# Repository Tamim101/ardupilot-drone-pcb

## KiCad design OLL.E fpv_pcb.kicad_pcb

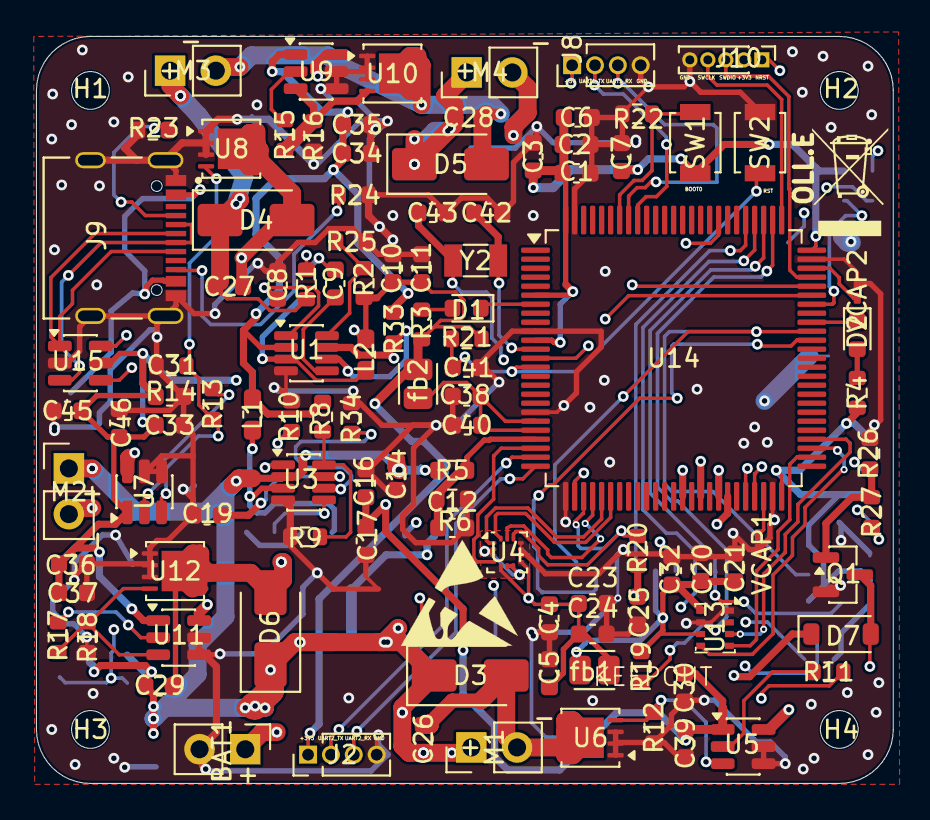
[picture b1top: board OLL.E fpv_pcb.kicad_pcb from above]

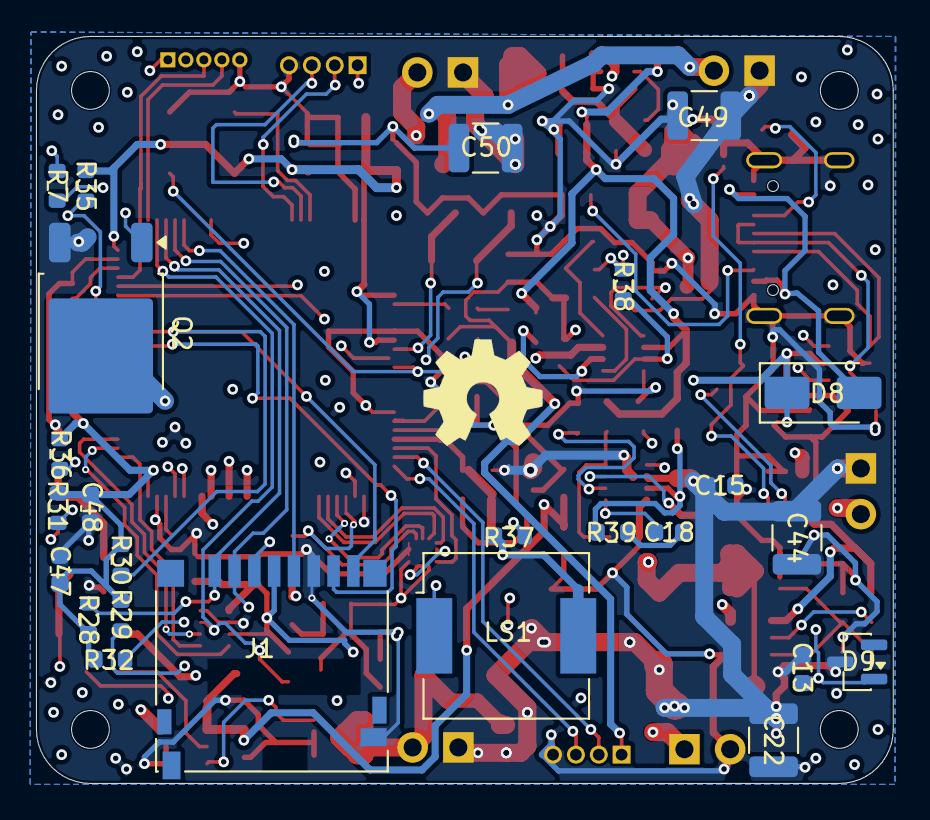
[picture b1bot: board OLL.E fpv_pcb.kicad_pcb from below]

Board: 6 copper layers, 47.6 x 41.5 mm, 138 parts (25 on the bottom side), 82 nets.

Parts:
BAT1: Conn_01x02_Pin; PinHeader_1x02_P2.54mm_Vertical
C1, C2, C3, C6, C8, C9, C12, C13, C14, C18, C19, C20, C32, C38, C41, C46, C47: 100nF; C_0603_1608Metric
C4, C33, C35, C37, C39, C40: 1uF; C_0603_1608Metric
C5, C15, C21, C48: 10uF; C_0603_1608Metric
C7, C11, C45: 4.7uF; C_0603_1608Metric
C10, C16: 22uF; C_0603_1608Metric
C17: 22uF/16v; C_0603_1608Metric
C22, C44, C49, C50: 22uF; C_1210_3225Metric
C23: 10nF; C_0603_1608Metric
C24: 0.1uF; C_0603_1608Metric
C25: 2.2uF; C_0603_1608Metric
C26, C27, C28, C29: 100nf; C_0603_1608Metric
C30, C31, C34, C36: 100nF/50v; C_0603_1608Metric
C42, C43: 15pF; C_0603_1608Metric
D1, D2: led; LED_0603_1608Metric
D3, D4, D5, D6: SS54FSH; D_SMA
D7: 1N4148W; D_SOD-123
D8: SS14; D_SMA
D9: BZX84C10; SOT-23
H1, H2, H3, H4: MountingHole; MountingHole_2.1mm
J1: Micro_SD_Card; microSD_HC_Hirose_DM3D-SF
J2: RC; PinHeader_1x04_P1.27mm_Vertical
J8: reciver; PinHeader_1x04_P1.27mm_Vertical
J9: TYPE-C-31-M-12; HRO_TYPE-C-31-M-12
J10: Conn_01x05_Pin; PinHeader_1x05_P1.00mm_Vertical
L1, L2: 4.7uH; L_0603_1608Metric_Pad1.05x0.95mm_HandSolder
LS1: CMT-7525-80-SMT-TR; Buzzer_CUI_CPT-9019S-SMT
M1: M1 front left; PinHeader_1x02_P2.54mm_Vertical
M2: M2 front right; PinHeader_1x02_P2.54mm_Vertical
M3: M3 rear right; PinHeader_1x02_P2.54mm_Vertical
M4: m4 rear left; PinHeader_1x02_P2.54mm_Vertical
Q1: 2N7002; SOT-23
Q2: SUD45P03-09; TO-252-2
R1, R10, R33: 100k; R_0603_1608Metric
R2: 31.6k; R_0603_1608Metric
R3, R4: 1k; R_0603_1608Metric
R5: 22k; R_0603_1608Metric
R6, R9, R12, R14, R16, R18, R20, R21, R22, R25, R26, R35, R36: 10k; R_0603_1608Metric
R7: 0 ohm; R_0603_1608Metric
R8: 52.3k; R_0603_1608Metric
R11, R13, R15, R17: 33; R_0603_1608Metric
R19: 10K; R_0603_1608Metric
R23, R24: 5.1k; R_0603_1608Metric
R27: 100; R_0603_1608Metric
R28, R29, R30, R31, R32: 47k; R_0603_1608Metric
R34: 33k; R_0603_1608Metric
R37: 18 ohm; R_0603_1608Metric
R38, R39: 20 ohm; R_0603_1608Metric
SW1, SW2: SW_SPST; SW_SPST_B3U-1000P
U1, U3: MP2315GJ; SOT-23-8
U4: ICM-42688-P; LGA-14_2x2mm_P0.35mm_LayoutBorder3x4y
U5, U7, U9, U11: UCC27511ADBV; SOT-23-6
U6: ul_AON7410; DFN-8-1EP_3x3mm_P0.65mm_EP1.5x2.25mm
U8, U10, U12: AON7410; DFN-8-1EP_3x3mm_P0.65mm_EP1.5x2.25mm
U13: BMP280; Bosch_LGA-8_2x2.5mm_P0.65mm_ClockwisePinNumbering
U14: STM32H753VITx; LQFP-100_14x14mm_P0.5mm
U15: USBLC6-2SC6; SOT-23-6
VCAP1, VCAP2: 2.2uF; C_0201_0603Metric_Pad0.64x0.40mm_HandSolder
Y2: 8HMz; Crystal_SMD_3215-2Pin_3.2x1.5mm
fb1, fb2: 600 ohm 100mHZ; L_Eaton_MCL2012V1

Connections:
+3V3_FC: C1.1 (+), C2.1 (+), C3.1 (+), C6.1 (+), C7.1 (+), C10.1 (+), C11.1 (+), C20.2 (-), C21.1 (+), C32.1 (+), C47.1 (+), C48.1 (+), J1.4 (VDD), J2.1, J10.2, L2.2 (-), R2.2 (-), R3.1 (+), R4.1 (+), R19.2 (-), R21.2 (-), R28.1 (+), R29.1 (+), R30.1 (+), R31.2 (-), R32.1 (+), R35.2 (-), R36.2 (-), SW1.1 (A), U13.6 (VDDIO), U13.8 (VDD), U14.6 (VBAT), U14.11 (VDD), U14.27 (VDD), U14.50 (VDD), U14.75 (VDD), U14.100 (VDD), fb1.2, fb2.1
+3V3_IMU: C4.1 (+), C5.1 (+), C23.1 (+), C24.1 (+), C25.2 (-), R20.1 (+), U4.5 (VDDIO), U4.8 (VDD), fb1.1
+5V_FC: C16.1 (+), C17.1 (+), C30.1 (+), C31.1 (+), C33.1 (+), C34.1 (+), C35.1 (+), C36.1 (+), C37.1 (+), C39.1 (+), C45.1 (+), C46.1 (+), D8.1 (K), J8.1, L1.2 (-), R8.2 (-), R33.2 (-), R37.1 (+), U1.2 (IN), U5.1 (V_{DD}), U7.1 (V_{DD}), U9.1 (V_{DD}), U11.1 (V_{DD}), U15.5 (VBUS)
+VBAT: C13.2 (-), C14.2 (-), C15.1 (+), C22.2 (-), C26.1 (+), C27.1 (+), C28.1 (+), C29.1 (+), C44.2 (-), C49.2 (-), C50.2 (-), D3.1, D4.1, D5.1, D6.1, D9.3 (K), M1.1, M2.1, M3.1, M4.1, Q2.3 (S), R1.1 (+), R5.2 (-), U3.2 (IN)
/VBAT_RAW: BAT1.1, Q2.2 (D)
ADC_VBAT: C12.1 (+), R5.1 (+), R6.2 (-), U14.22 (PA0)
BARO_CS: R19.1 (+), U13.2 (CSB), U14.77 (PA15)
BEEPER: R27.1 (+), U14.46 (PB10)
BOOT0: R22.2 (-), SW1.2 (B), U14.94 (BOOT0)
C1_D0: J1.7 (DAT0), R29.2 (-), U14.65 (PC8)
C1_D1: J1.8 (DAT1), R30.2 (-), U14.66 (PC9)
C1_D2: J1.1 (DAT2), R28.2 (-), U14.78 (PC10)
C1_D3: J1.2 (DAT3/CD), R32.2 (-), U14.79 (PC11)
CLK: J1.5 (CLK), U14.80 (PC12)
CMD: J1.3 (CMD), R31.1 (+), U14.83 (PD2)
GND: BAT1.2, C1.2 (-), C2.2 (-), C3.2 (-), C4.2 (-), C5.2 (-), C6.2 (-), C7.2 (-), C8.2 (-), C10.2 (-), C11.2 (-), C12.2 (-), C14.1 (+), C15.2 (-), C16.2 (-), C17.2 (-), C19.2 (-), C20.1 (+), C21.2 (-), C22.1 (+), C23.2 (-), C24.2 (-), C25.1 (+), C30.2 (-), C31.2 (-), C32.2 (-), C33.2 (-), C34.2 (-), C35.2 (-), C36.2 (-), C37.2 (-), C38.2 (-), C39.2 (-), C40.2 (-), C41.2 (-), C42.2 (-), C43.2 (-), C44.1 (+), C45.2 (-), C46.2 (-), C47.2 (-), C48.2 (-), C49.1 (+), C50.1 (+), J1.6 (VSS), J1.9 (SHIELD), J2.4, J8.4, J9.A1_B12 (GND), J9.B1_A12 (GND), J9.S1 (SHIELD), J9.S2 (SHIELD), J9.S3 (SHIELD), J9.S4 (SHIELD), J10.5, Q1.2 (S), R6.1 (+), R9.1 (+), R10.2 (-), R12.2 (-), R14.2 (-), R16.2 (-), R18.2 (-), R22.1 (+), R23.1 (+), R24.1 (+), R25.1 (+), R26.2 (-), R34.2 (-), SW2.2 (B), U1.4 (GND), U3.4 (GND), U4.2 (RESV_2), U4.3 (RESV_3), U4.6 (GND), U4.7 (RESV_7), U4.9 (INT2/FSYNC/CLKIN), U4.10 (RESV_10), U4.11 (RESV_11), U5.4 (GND), U5.5 (IN-), U6.1 (S), U6.2 (S), U6.3 (S), U7.4 (GND), U7.5 (IN-), U8.1 (S), U8.2 (S), U8.3 (S), U9.4 (GND), U9.5 (IN-), U10.1 (S), U10.2 (S), U10.3 (S), U11.4 (GND), U11.5 (IN-), U12.1 (S), U12.2 (S), U12.3 (S), U13.1 (GND), U13.7 (GND), U14.10 (VSS), U14.19 (VSSA), U14.26 (VSS), U14.49 (VSS), U14.74 (VSS), U14.99 (VSS), U15.2 (GND), VCAP1.1 (+), VCAP2.1 (+)
GYRO_CS: R20.2 (-), U4.12 (AP_CS), U14.28 (PA4)
GYRO_INT: U4.4 (INT1/INT), U14.23 (PA1)
LED0: D1.1, U14.7 (PC13)
LED1_ARM: D2.1, U14.67 (PA8)
MOTOR1: U5.6 (IN+), U14.39 (PE9)
MOTOR2: U7.6 (IN+), U14.41 (PE11)
MOTOR3: U9.6 (IN+), U14.43 (PE13)
MOTOR4: U11.6 (IN+), U14.44 (PE14)
NRST: C41.1 (+), J10.1, R21.1 (+), SW2.1 (A), U14.14 (NRST)
unnamed: C8.1 (+), U1.1 (AAM), U1.7 (VCC)
unnamed: C9.1 (+), U1.5 (BST)
unnamed: C9.2 (-), R38.1 (+)
unnamed: C13.1 (+), D9.1 (A), Q2.1 (G), R10.1 (+)
unnamed: C18.1 (+), U3.5 (BST)
unnamed: C18.2 (-), R39.1 (+)
unnamed: C19.1 (+), U3.1 (AAM), U3.7 (VCC)
unnamed: C26.2 (-), D3.2, M1.2, U6.5 (D), U6.6 (D), U6.7 (D), U6.8 (D), U6.9 (EPAD)
unnamed: C27.2 (-), D4.2, M2.2, U8.5 (D), U8.6 (D), U8.7 (D), U8.8 (D), U8.9 (EPAD)
unnamed: C28.2 (-), D5.2, M3.2, U10.5 (D), U10.6 (D), U10.7 (D), U10.8 (D), U10.9 (EPAD)
unnamed: C29.2 (-), D6.2, M4.2, U12.5 (D), U12.6 (D), U12.7 (D), U12.8 (D), U12.9 (EPAD)
unnamed: C42.1 (+), U14.12 (PH0), Y2.1
unnamed: C43.1 (+), R7.1 (+), Y2.2
unnamed: D7.2 (A), LS1.1, Q1.3 (D)
unnamed: D7.1 (K), LS1.2, R37.2 (-)
unnamed: J9.A5 (CC1), R23.2 (-)
unnamed: J9.B5 (CC2), R24.2 (-)
unnamed: J9.A7 (DN1), J9.B7 (DN2), U15.3 (I/O2)
unnamed: J9.A6 (DP1), J9.B6 (DP2), U15.1 (I/O1)
unnamed: L1.1 (+), R39.2 (-), U3.3 (SW)
unnamed: L2.1 (+), R38.2 (-), U1.3 (SW)
unnamed: Q1.1 (G), R26.1 (+), R27.2 (-)
unnamed: R1.2 (-), R34.1 (+), U3.6 (EN/SYNC)
unnamed: R2.1 (+), R25.2 (-), U1.8 (FB)
unnamed: D1.2, R3.2 (-)
unnamed: D2.2, R4.2 (-)
unnamed: R7.2 (-), U14.13 (PH1)
unnamed: R8.1 (+), R9.2 (-), U3.8 (FB)
unnamed: R11.1 (+), R12.1 (+), U5.3 (OUTL), U6.4 (G)
unnamed: R11.2 (-), U5.2 (OUTH)
unnamed: R13.1 (+), R14.1 (+), U7.3 (OUTL), U8.4 (G)
unnamed: R13.2 (-), U7.2 (OUTH)
unnamed: R15.1 (+), R16.1 (+), U9.3 (OUTL), U10.4 (G)
unnamed: R15.2 (-), U9.2 (OUTH)
unnamed: R17.1 (+), R18.1 (+), U11.3 (OUTL), U12.4 (G)
unnamed: R17.2 (-), U11.2 (OUTH)
unnamed: R33.1 (+), U1.6 (EN/SYNC)
unnamed: R35.1 (+), U14.69 (PA10)
unnamed: R36.1 (+), U14.47 (PB11)
unnamed: U14.48 (VCAP), VCAP1.2 (-)
unnamed: U14.73 (VCAP), VCAP2.2 (-)
SPI1_SCK: U4.13 (AP_SCL/AP_SCLK), U14.29 (PA5)
SPI1_SDI: U4.14 (AP_SDA/AP_SDIO/AP_SDI), U14.31 (PA7)
SPI1_SDO: U4.1 (AP_SDO/AP_AD0), U14.30 (PA6)
SPI2_SCK: U13.4 (SCK), U14.52 (PB13)
SPI2_SDI: U13.3 (SDI), U14.54 (PB15)
SPI2_SDO: U13.5 (SDO), U14.53 (PB14)
SWCLK: J10.4, U14.76 (PA14)
SWDIO: J10.3, U14.72 (PA13)
UART1_RX: J8.3, U14.93 (PB7)
UART1_TX: J8.2, U14.92 (PB6)
UART2_RX: J2.3, U14.25 (PA3)
UART2_TX: J2.2, U14.24 (PA2)
USB D+: U14.71 (PA12), U15.6 (I/O1)
USB D−: U14.70 (PA11), U15.4 (I/O2)
VBUS: D8.2 (A), J9.A4_B9 (VBUS), J9.B4_A9 (VBUS)
VDDA_FILT: C38.1 (+), C40.1 (+), U14.20 (VREF+), U14.21 (VDDA), fb2.2

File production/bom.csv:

Designator,Footprint,Quantity,Value,LCSC Part #
BAT1,PinHeader_1x02_P2.54mm_Vertical,1,Conn_01x02_Pin,
"C1, C12, C13, C14, C18, C19, C2, C20, C26, C27, C28, C29, C3, C32, C38, C41, C46, C47, C6, C8, C9",0603,21,100nF,
"C10, C16",0603,2,22uF,
"C11, C45, C7",0603,3,4.7uF,
"C15, C21, C48, C5",0603,4,10uF,
C17,0603,1,22uF/16v,
"C22, C44, C49, C50",1210,4,22uF,
C23,0603,1,10nF,
C24,0603,1,0.1uF,
C25,0603,1,2.2uF,
"C30, C31, C34, C36",0603,4,100nF/50v,
"C33, C35, C37, C39, C4, C40",0603,6,1uF,
"C42, C43",0603,2,15pF,
"D1, D2",0603,2,led,
"D3, D4, D5, D6",D_SMA,4,SS54FSH,
D7,D_SOD-123,1,1N4148W,
D8,D_SMA,1,SS14,
D9,SOT-23,1,BZX84C10,
"FB1, FB2",L_Eaton_MCL2012V1,2,600 ohm 100mHZ,
J1,microSD_HC_Hirose_DM3D-SF,1,Micro_SD_Card,
J10,PinHeader_1x05_P1.00mm_Vertical,1,Conn_01x05_Pin,
J2,PinHeader_1x04_P1.27mm_Vertical,1,RC,
J8,PinHeader_1x04_P1.27mm_Vertical,1,reciver,
J9,HRO_TYPE-C-31-M-12,1,TYPE-C-31-M-12,
"L1, L2",0603,2,4.7uH,
LS1,Buzzer_CUI_CPT-9019S-SMT,1,CMT-7525-80-SMT-TR,
M1,PinHeader_1x02_P2.54mm_Vertical,1,M1 front left,
M2,PinHeader_1x02_P2.54mm_Vertical,1,M2 front right,
M3,PinHeader_1x02_P2.54mm_Vertical,1,M3 rear right,
M4,PinHeader_1x02_P2.54mm_Vertical,1,m4 rear left,
Q1,SOT-23,1,2N7002,
Q2,TO-252-2,1,SUD45P03-09,
"R1, R10, R33",0603,3,100k,
"R11, R13, R15, R17",0603,4,33,
"R12, R14, R16, R18, R19, R20, R21, R22, R25, R26, R35, R36, R6, R9",0603,14,10k,
R2,0603,1,31.6k,
"R23, R24",0603,2,5.1k,
R27,0603,1,100,
"R28, R29, R30, R31, R32",0603,5,47k,
"R3, R4",0603,2,1k,
R34,0603,1,33k,
R37,0603,1,18 ohm,
"R38, R39",0603,2,20 ohm,
R5,0603,1,22k,
R7,0603,1,0 ohm,
R8,0603,1,52.3k,
"SW1, SW2",SW_SPST_B3U-1000P,2,SW_SPST,
"U1, U3",SOT-23-8,2,MP2315GJ,MP2315
"U10, U12, U8",DFN-8-1EP_3x3mm_P0.65mm_EP1.5x2.25mm,3,AON7410,
"U11, U5, U7, U9",SOT-23-6,4,UCC27511ADBV,
U13,Bosch_LGA-8_2x2.5mm_P0.65mm_ClockwisePinNumbering,1,BMP280,
U14,LQFP-100_14x14mm_P0.5mm,1,STM32H753VITx,
U15,SOT-23-6,1,USBLC6-2SC6,
U4,LGA-14_2x2mm_P0.35mm_LayoutBorder3x4y,1,ICM-42688-P,
U6,DFN-8-1EP_3x3mm_P0.65mm_EP1.5x2.25mm,1,ul_AON7410,
"VCAP1, VCAP2",0201,2,2.2uF,
Y2,Crystal_SMD_3215-2Pin_3.2x1.5mm,1,8HMz,
